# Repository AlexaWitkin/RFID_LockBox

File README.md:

# RFID_LockBox
### Abstract 
This project presents the design and implementation of a compact RFID-controlled lockbox intended to provide secure personal storage for an end user sharing a living space with a roommate. The goal was to create a reliable, stand-alone access-control system while gaining hands-on experience working with the ATmega328P as a discrete microcontroller rather than relying on a full Arduino development board. The system integrates an RC522 RFID reader operating at 13.56 MHz, a custom-designed PCB incorporating power regulation, logic-level shifting, and microcontroller support circuitry, and a servo-based mechanical locking mechanism housed within a laser-cut wooden enclosure. Throughout development, particular attention was given to power constraints, signal-integrity challenges between 5V and 3.3V domains, and practical issues such as servo initialization and UID formatting. The final design successfully demonstrates a functional, durable lockbox that reliably authenticates RFID tags and actuates a locking mechanism, achieving the project’s objectives in both usability and technical learning.

** For more information view 'CMPE 3185 Final Project.pdf'

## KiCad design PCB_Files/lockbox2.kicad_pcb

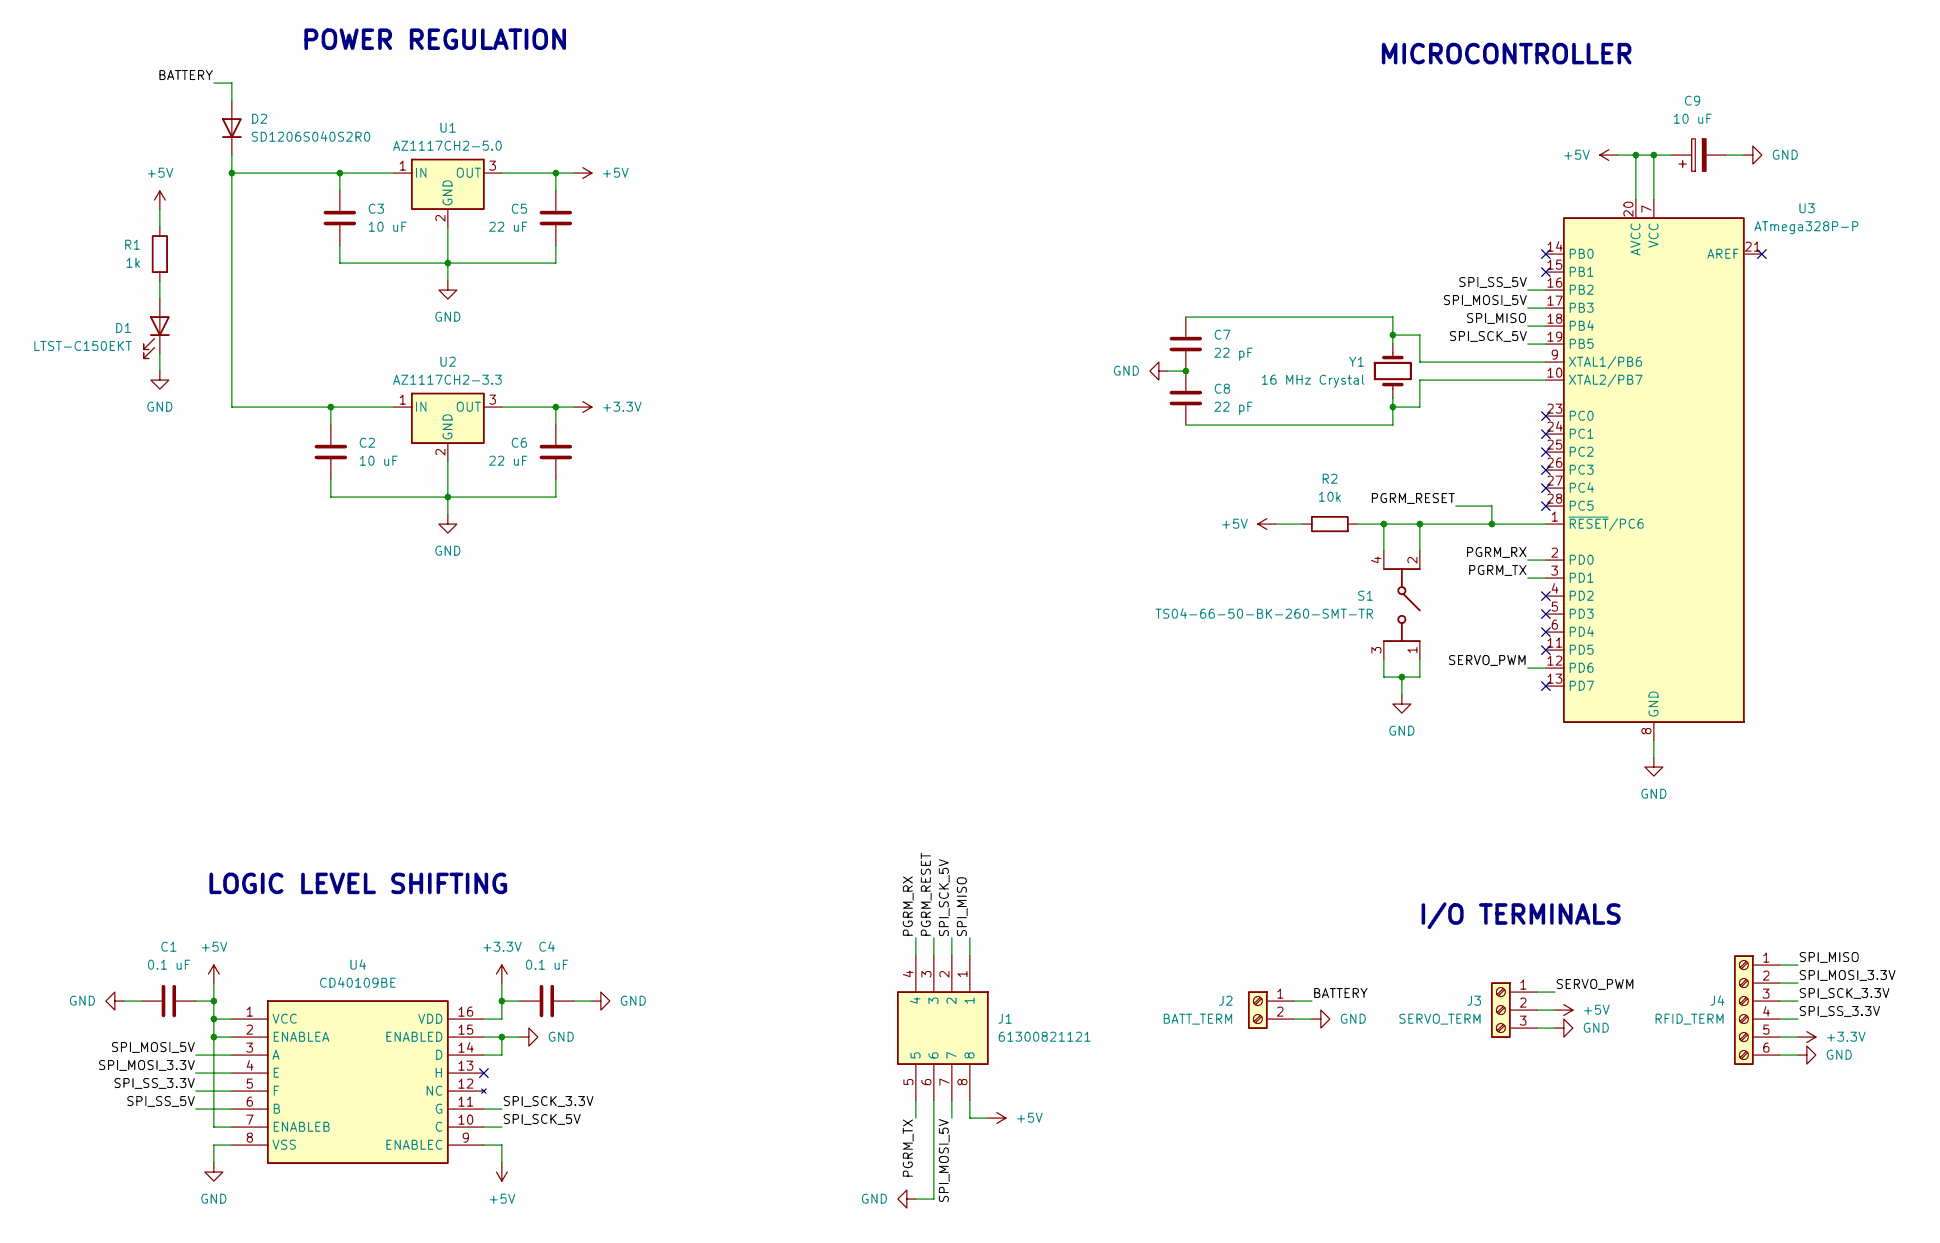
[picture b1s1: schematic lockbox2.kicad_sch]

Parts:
C1, C4: 0.1 uF; C_1206_3216Metric_Pad1.33x1.80mm_HandSolder
C2, C3: 10 uF; C_1206_3216Metric_Pad1.33x1.80mm_HandSolder
C5, C6: 22 uF; C_1206_3216Metric_Pad1.33x1.80mm_HandSolder
C7, C8: 22 pF; C_1206_3216Metric_Pad1.33x1.80mm_HandSolder
C9: 10 uF; CP_Radial_D5.0mm_P2.00mm
D1: LTST-C150EKT; LED_1206_3216Metric_Pad1.42x1.75mm_HandSolder
D2: SD1206S040S2R0; D_1206_3216Metric_Pad1.42x1.75mm_HandSolder
J1: 61300821121; Manufacturer_Part_Number 61300821121; Mouser Part Number 710-61300821121
J2: BATT_TERM; TerminalBlock_Phoenix_PT-1,5-2-5.0-H_1x02_P5.00mm_Horizontal
J3: SERVO_TERM; TerminalBlock_Phoenix_PT-1,5-3-5.0-H_1x03_P5.00mm_Horizontal
J4: RFID_TERM; TerminalBlock_Phoenix_PT-1,5-6-5.0-H_1x06_P5.00mm_Horizontal
R1: 1k; R_1206_3216Metric_Pad1.30x1.75mm_HandSolder
R2: 10k; R_1206_3216Metric_Pad1.30x1.75mm_HandSolder
S1: TS04-66-50-BK-260-SMT-TR; TS046650BK260SMTTR; Manufacturer_Part_Number TS04-66-50-BK-260-SMT-TR; Mouser Part Number 179-TS046650BK260SMR
U1: AZ1117CH2-5.0; SOT-223-3_TabPin2
U2: AZ1117CH2-3.3; SOT-223-3_TabPin2
U3: ATmega328P-P; DIP-28_W7.62mm
U4: CD40109BE; DIP794W53P254L1930H508Q16N; Manufacturer_Part_Number CD40109BE; Mouser Part Number 595-CD40109BE
Y1: 16 MHz Crystal; Crystal_HC49-U_Vertical

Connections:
+3.3V: C4.1, C6.1, J4.5, U2.3 (OUT), U4.16 (VDD)
+5V: C1.2, C5.1, C9.1, J1.8, J3.2, R1.1, R2.1, U1.3 (OUT), U3.7 (VCC), U3.20 (AVCC), U4.1 (VCC), U4.2 (ENABLEA), U4.7 (ENABLEB), U4.9 (ENABLEC)
/BATTERY: D2.2 (A), J2.1
/PGRM_RESET: J1.3, R2.2, S1.2 (COM_1), S1.4 (COM_2), U3.1 (~RESET/PC6)
/PGRM_RX: J1.4, U3.2 (PD0)
/PGRM_TX: J1.5, U3.3 (PD1)
/SERVO_PWM: J3.1, U3.12 (PD6)
/SPI_MISO: J1.1, J4.1, U3.18 (PB4)
/SPI_MOSI_3.3V: J4.2, U4.4 (E)
/SPI_MOSI_5V: J1.7, U3.17 (PB3), U4.3 (A)
/SPI_SCK_3.3V: J4.3, U4.11 (G)
/SPI_SCK_5V: J1.2, U3.19 (PB5), U4.10 (C)
/SPI_SS_3.3V: J4.4, U4.5 (F)
/SPI_SS_5V: U3.16 (PB2), U4.6 (B)
GND: C1.1, C2.2, C3.2, C4.2, C5.2, C6.2, C7.2, C8.1, C9.2, D1.1 (K), J1.6, J2.2, J3.3, J4.6, S1.1 (NO_1), S1.3 (NO_2), U1.2 (GND), U2.2 (GND), U3.8 (GND), U3.22 (GND), U4.8 (VSS), U4.14 (D), U4.15 (ENABLED)
unnamed: D1.2 (A), R1.2
unnamed: C2.1, C3.1, D2.1 (K), U1.1 (IN), U2.1 (IN)
unnamed: C7.1, U3.9 (XTAL1/PB6), Y1.1
unnamed: C8.2, U3.10 (XTAL2/PB7), Y1.2

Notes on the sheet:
I/O TERMINALS
MICROCONTROLLER
POWER REGULATION
LOGIC LEVEL SHIFTING

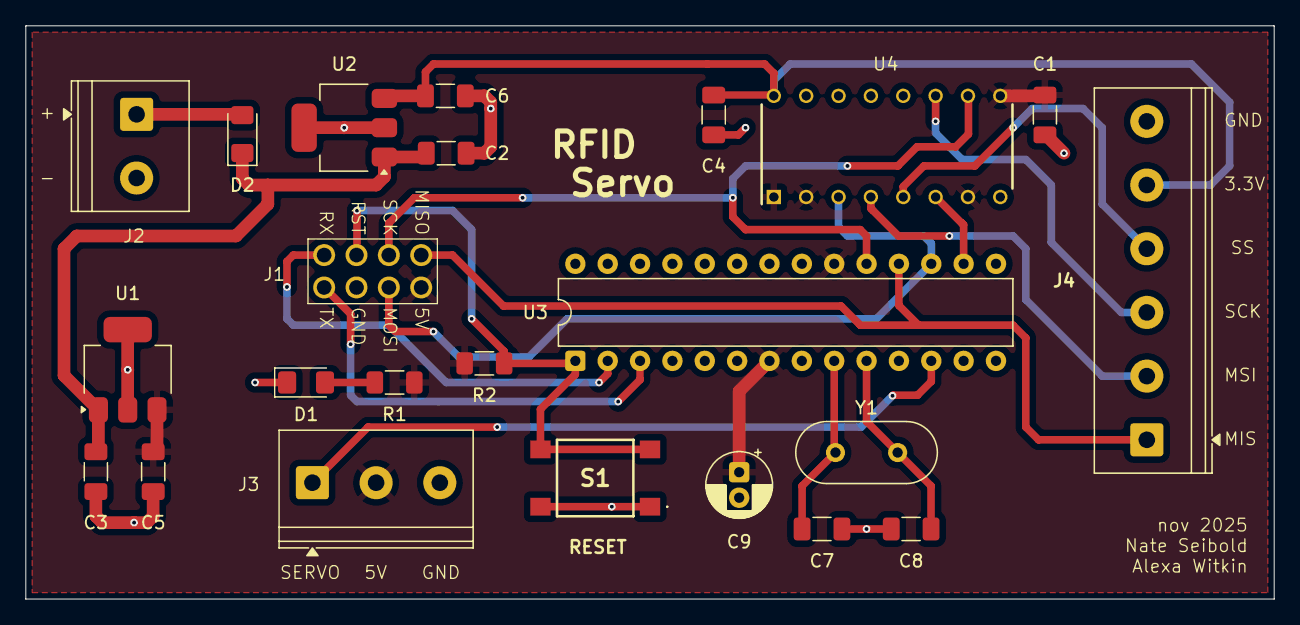
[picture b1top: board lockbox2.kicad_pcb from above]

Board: 2 copper layers, 98.0 x 45.0 mm, 23 parts (0 on the bottom side), 19 nets.

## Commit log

2025-12-01 Added current working main and servo/rfid function files
2025-12-12 Files for PCB
    PCB files for manufacturing. Be aware, there are issues with the design that have not been fixed.
2025-12-12 specify purpose
2025-12-12 delay 10 sec not 1 min + delete old version of function
    Updated delay duration and removed unused servo function.
2025-12-12 Final Project Report
2025-12-12 added report abstract to readme
2025-12-12 adding .svg files for laser cut boxes
2025-12-12 individual files moved to folders
